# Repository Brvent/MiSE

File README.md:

## Projecte MiSE
L'objectiu principal d'aquesta asignatura es el desenvolupament del hardware i el software d'un sistema que permeti controlar els moviments d'un robot amb un microcontrolador MSP430FR2355TPT.

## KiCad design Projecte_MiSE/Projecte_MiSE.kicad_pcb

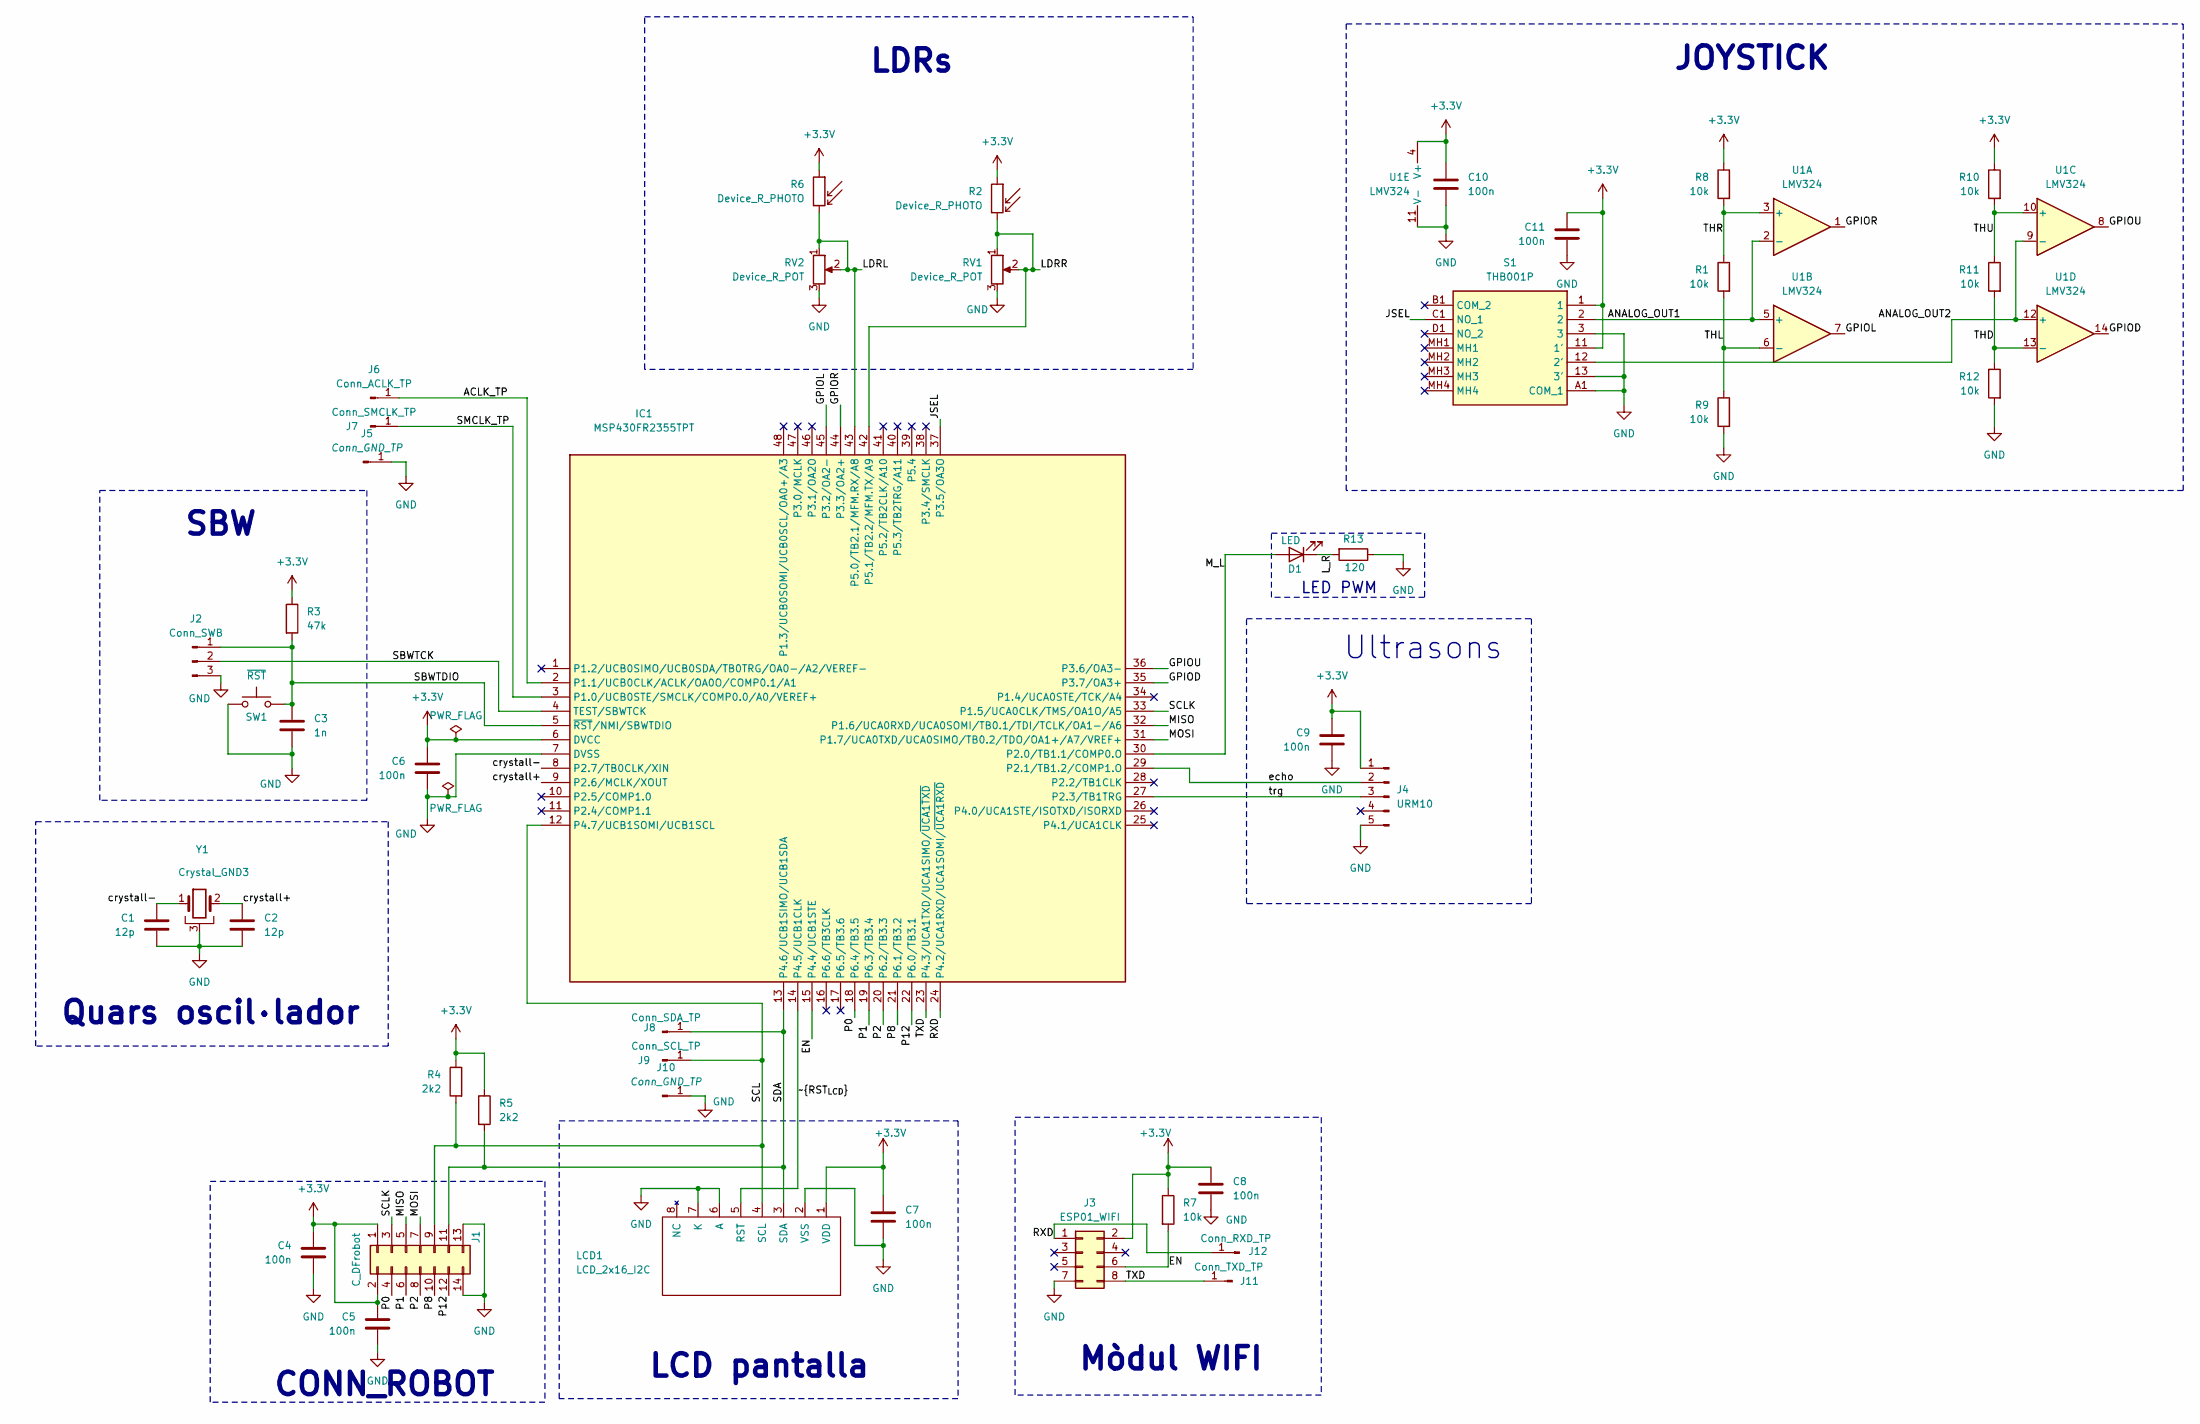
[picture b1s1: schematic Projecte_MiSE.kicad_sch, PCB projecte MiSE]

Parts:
C1, C2: 12p; C_0805_2012Metric
C3: 1n; C_0805_2012Metric
C4, C5, C6, C7, C8, C9, C10, C11: 100n; C_0805_2012Metric
D1: LED; LED_0805_2012Metric
IC1: MSP430FR2355TPT; LQFP-48_7x7mm_P0.5mm; Manufacturer_Part_Number MSP430FR2355TPT; Mouser Part Number 595-MSP430FR2355TPT
J1: C_DFrobot; conn_DFrobot
J2: Conn_SWB; PinHeader_1x03_P2.54mm_Vertical
J3: ESP01_WIFI; PinSocket_2x04_P2.54mm_Vertical
J4: URM10; PinHeader_1x05_P2.54mm_Vertical
J5, J10: Conn_GND_TP; PinHeader_1x01_P2.54mm_Vertical
J6: Conn_ACLK_TP; PinHeader_1x01_P2.54mm_Vertical
J7: Conn_SMCLK_TP; PinHeader_1x01_P2.54mm_Vertical
J8: Conn_SDA_TP; PinHeader_1x01_P2.54mm_Vertical
J9: Conn_SCL_TP; PinHeader_1x01_P2.54mm_Vertical
J11: Conn_TXD_TP; PinHeader_1x01_P2.54mm_Vertical
J12: Conn_RXD_TP; PinHeader_1x01_P2.54mm_Vertical
LCD1: LCD_2x16_I2C; LCD_2x16_I2C(Midas)
R1, R7, R8, R9, R10, R11, R12: 10k; R_0805_2012Metric
R2, R6: Device_R_PHOTO; LDR
R3: 47k; R_0805_2012Metric
R4, R5: 2k2; R_0805_2012Metric
R13: 120; R_0805_2012Metric
RV1, RV2: Device_R_POT; Trimmer_MiSE
S1: THB001P; Manufacturer_Part_Number THB001P; Mouser Part Number 611-THB001P
SW1: ~{RST}; SW_PUSH_6mm
U1: LMV324; SOIC-14_3.9x8.7mm_P1.27mm
Y1: Crystal_GND3; Crystal_DS26_D2.0mm_L6.0mm_Horizontal_1EP_style1

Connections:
+3.3V: C4.1, C5.1, C6.1, C7.1, C8.1, C9.1, C10.1, C11.1, IC1.6 (DVCC), J1.1, J1.2, J3.2, J4.1, LCD1.1 (VDD), R2.1, R3.1, R4.1, R5.1, R6.1, R7.1, R8.1, R10.1, S1.1, S1.11 (1'), U1.4 (V+)
/ACLK_TP: IC1.2 (P1.1/UCB0CLK/ACLK/OA0O/COMP0.1/A1), J6.1
/ANALOG_OUT1: S1.2, U1.2 (-), U1.5 (+)
/ANALOG_OUT2: S1.12 (2'), U1.9 (-), U1.12 (+)
/EN: IC1.15 (P4.4/UCB1STE), J3.6, R7.2
/GPIOD: IC1.35 (P3.7/OA3+), U1.14
/GPIOL: IC1.45 (P3.2/OA2-), U1.7
/GPIOR: IC1.44 (P3.3/OA2+), U1.1
/GPIOU: IC1.36 (P3.6/OA3-), U1.8
/JSEL: IC1.37 (P3.5/OA3O), S1.C1 (NO_1)
/LDRL: IC1.43 (P5.0/TB2.1/MFM.RX/A8), R6.2, RV2.1, RV2.2
/LDRR: IC1.42 (P5.1/TB2.2/MFM.TX/A9), R2.2, RV1.1, RV1.2
/L_R: D1.1 (K), R13.2
/MISO: IC1.32 (P1.6/UCA0RXD/UCA0SOMI/TB0.1/TDI/TCLK/OA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), J1.5
/MOSI: IC1.31 (P1.7/UCA0TXD/UCA0SIMO/TB0.2/TDO/OA1+/A7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), J1.7
/M_L: D1.2 (A), IC1.30 (P2.0/TB1.1/COMP0.O)
/P0: IC1.18 (P6.4/TB3.5), J1.4
/P1: IC1.19 (P6.3/TB3.4), J1.6
/P2: IC1.20 (P6.2/TB3.3), J1.8
/P8: IC1.21 (P6.1/TB3.2), J1.10
/P12: IC1.22 (P6.0/TB3.1), J1.12
/RXD: IC1.24 (P4.2/UCA1RXD/UCA1SOMI/~UCA1RXD), J3.1, J12.1
/SBWTCK: IC1.4 (TEST/SBWTCK), J2.2
/SBWTDIO: C3.1, IC1.5 (~RST/NMI/SBWTDIO), J2.1, R3.2, SW1.2
/SCL: IC1.12 (P4.7/UCB1SOMI/UCB1SCL), J1.9, J9.1, LCD1.4 (SCL), R4.2
/SCLK: IC1.33 (P1.5/UCA0CLK/TMS/OA1O/A5), J1.3
/SDA: IC1.13 (P4.6/UCB1SIMO/UCB1SDA), J1.11, J8.1, LCD1.3 (SDA), R5.2
/SMCLK_TP: IC1.3 (P1.0/UCB0STE/SMCLK/COMP0.0/A0/VEREF+), J7.1
/THD: R11.2, R12.1, U1.13 (-)
/THL: R1.2, R9.1, U1.6 (-)
/THR: R1.1, R8.2, U1.3 (+)
/THU: R10.2, R11.1, U1.10 (+)
/TXD: IC1.23 (P4.3/UCA1TXD/UCA1SIMO/~UCA1TXD), J3.8, J11.1
/crystall+: C2.1, IC1.9 (P2.6/MCLK/XOUT), Y1.2
/crystall-: C1.1, IC1.8 (P2.7/TB0CLK/XIN), Y1.1
/echo: IC1.29 (P2.1/TB1.2/COMP1.O), J4.2
/trg: IC1.27 (P2.3/TB1TRG), J4.3
/~RST_{LCD}: IC1.14 (P4.5/UCB1CLK), LCD1.5 (RST)
GND: C1.2, C2.2, C3.2, C4.2, C5.2, C6.2, C7.2, C8.2, C9.2, C10.2, C11.2, IC1.7 (DVSS), J1.13, J1.14, J2.3, J3.7, J4.5, J5.1, J10.1, LCD1.2 (VSS), LCD1.6 (A), LCD1.7 (K), R9.2, R12.2, R13.1, RV1.3, RV2.3, S1.3, S1.13 (3'), S1.A1 (COM_1), SW1.1, U1.11 (V-), Y1.3

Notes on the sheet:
SBW
JOYSTICK
Ultrasons
Mòdul WIFI
LDRs
LED PWM
CONN_ROBOT
LCD pantalla
Quars oscil·lador

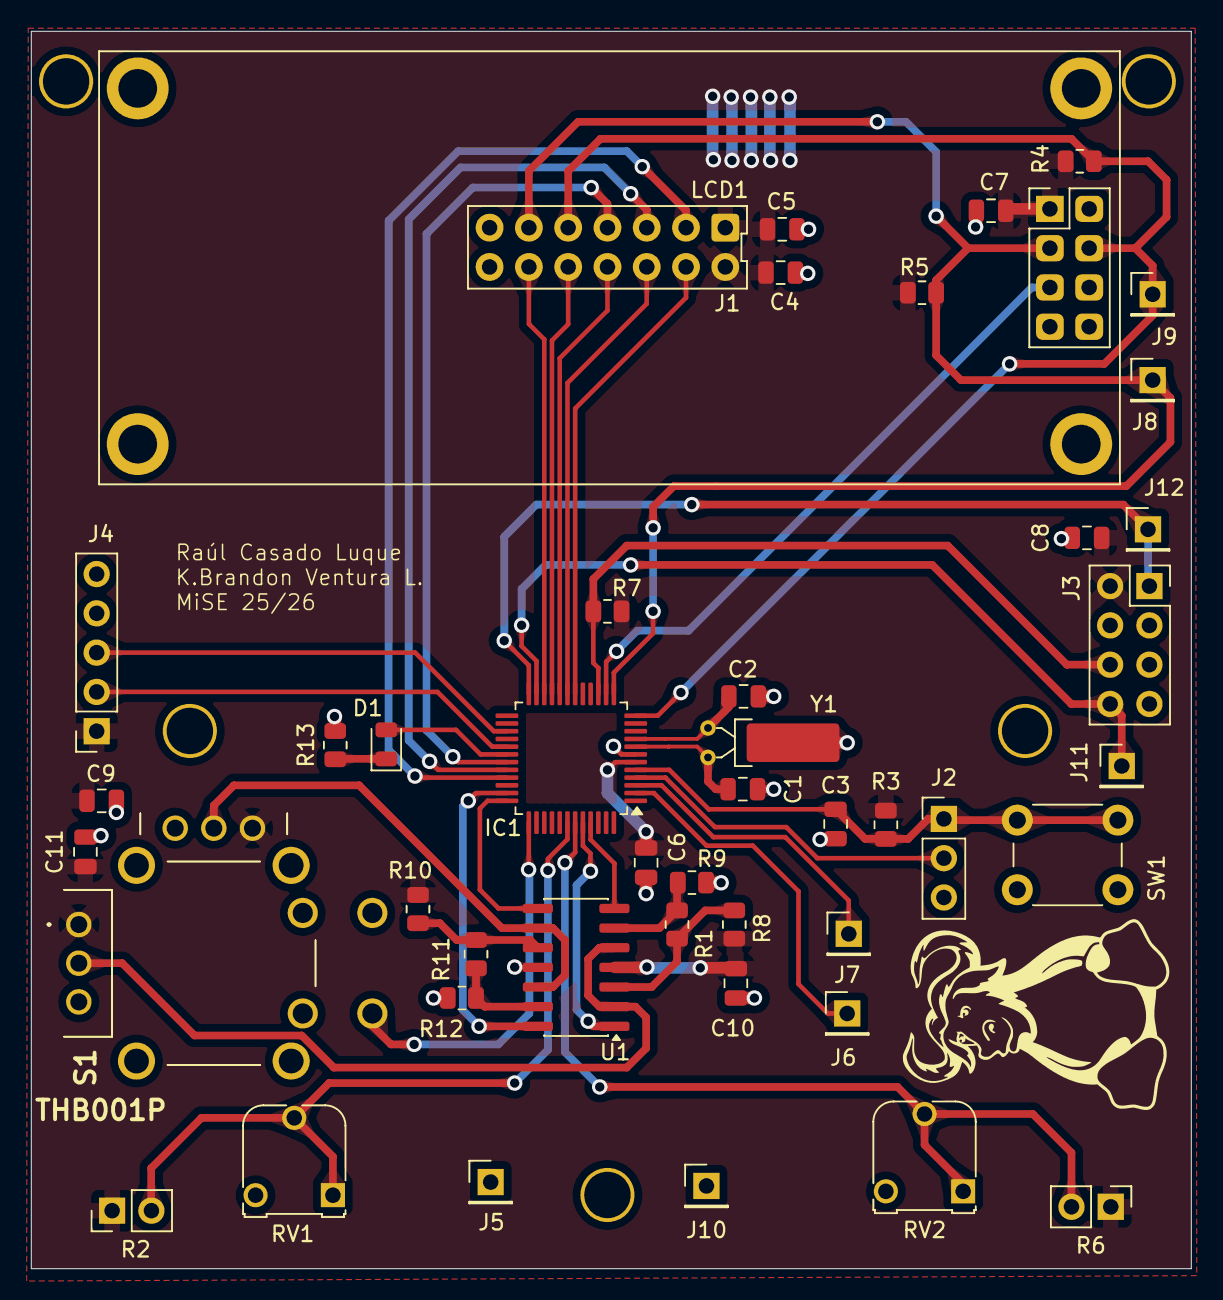
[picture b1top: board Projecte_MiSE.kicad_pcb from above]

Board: 2 copper layers, 75.0 x 80.0 mm, 45 parts (0 on the bottom side), 39 nets.

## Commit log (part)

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2026-03-03 projecte
2026-03-03 components add
2026-03-03 LAYOUT_RULES
2026-03-06 layout LCD i DFrobot
2026-03-06 proyecto
2026-03-10 test point added
2026-03-10 test point added & net classes types
2026-03-10 footprints and layout
2026-03-10 layout and schem pins
2026-03-13 relocated pins and added power flags
    ERC check
2026-03-13 component placement and routing
    DRC, constrains and net classes. minor details are missing
2026-03-13 netclasses
2026-03-13 Crystal
2026-03-15 Routing correction
